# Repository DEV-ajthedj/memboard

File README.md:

# memboard
A custom development board aimed at maximizing the RAM of an RP2354A. I am doing this because I am currently developing a 3D graphics pipeline (very experimental) for microcontrollers, and an upgrade from the 264 KB Pico would be very nice for larger frambuffers and 3D objects. This is also why I didn't really need much flash on the board, so I just went with the RP2354A, which has 2MB of flash already built in. This project is meant for me to be able to really start developing and testing my pipeline more, without being limited by memory.

# Future Improvements
In the future, I hope to make firmware to make this microcontroller stackable. This could (hopefully) substantially increase the maximum compute it could generate.

# Preview

# Routing

# Schematic

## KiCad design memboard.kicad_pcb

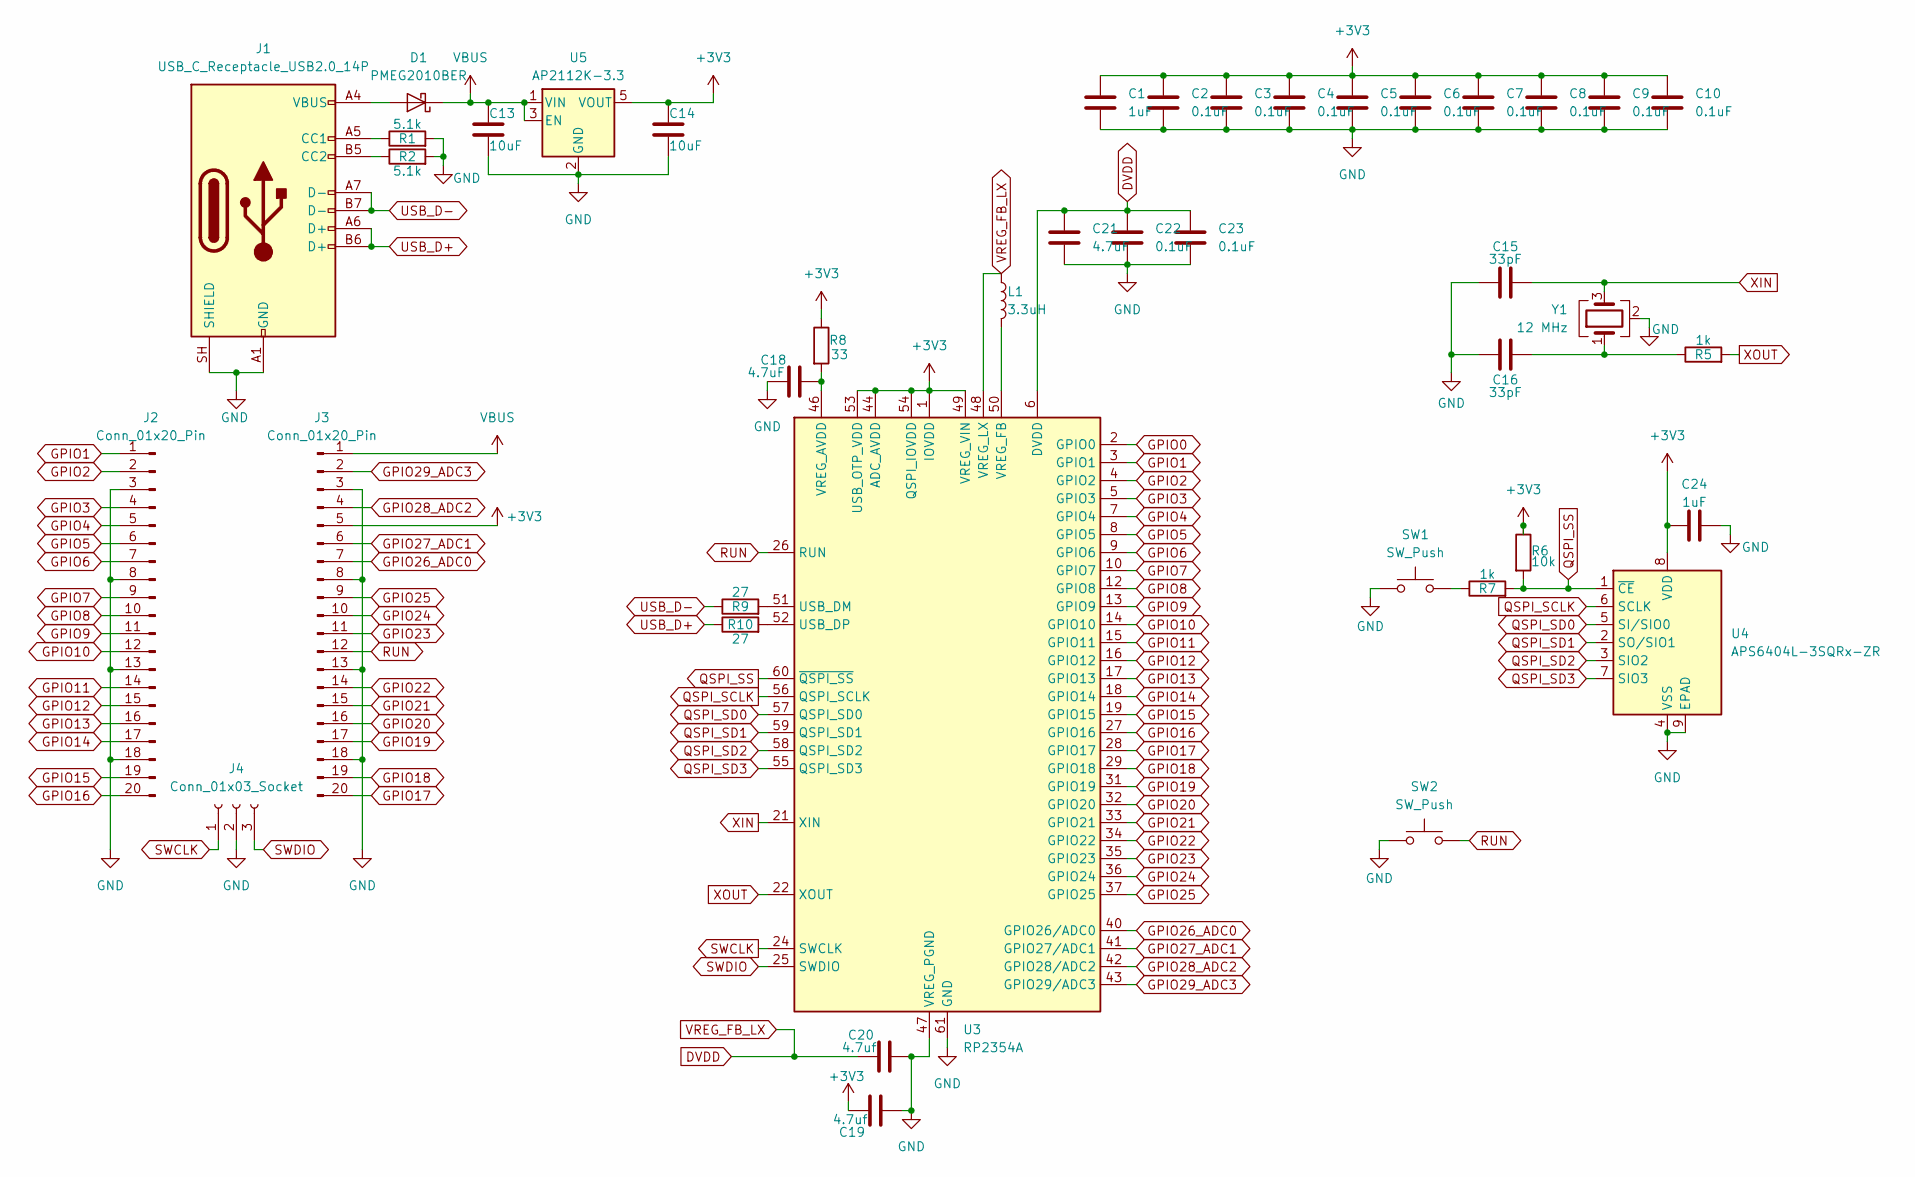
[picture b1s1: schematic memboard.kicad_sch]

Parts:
C1, C24: 1uF; C_0402_1005Metric
C2, C3, C4, C5, C6, C7, C8, C9, C10, C22, C23: 0.1uF; C_0402_1005Metric
C13, C14: 10uF; C_0603_1608Metric
C15, C16: 33pF; C_0402_1005Metric
C18, C21: 4.7uF; C_0603_1608Metric
C19, C20: 4.7uf; C_0603_1608Metric
D1: PMEG2010BER; Nexperia_CFP3_SOD-123W
J1: USB_C_Receptacle_USB2.0_14P; USB_C_Receptacle_HRO_TYPE-C-31-M-12
J2, J3: Conn_01x20_Pin; PinHeader_1x20_P2.54mm_Vertical
J4: Conn_01x03_Socket; PinSocket_1x03_P2.54mm_Vertical
L1: 3.3uH; L_0805_2012Metric
R1, R2: 5.1k; R_0402_1005Metric
R5, R7: 1k; R_0402_1005Metric
R6: 10k; R_0402_1005Metric
R8: 33; R_0402_1005Metric
R9, R10: 27; R_0402_1005Metric
SW1, SW2: SW_Push; SW_Push_SPST_NO_Alps_SKRK
U3: RP2354A; QFN-60-1EP_7x7mm_P0.4mm_EP3.4x3.4mm
U4: APS6404L-3SQRx-ZR; Winbond_USON-8-1EP_3x2mm_P0.5mm_EP0.2x1.6mm
U5: AP2112K-3.3; SOT-23-5
Y1: 12 MHz; Crystal_SMD_3225-4Pin_3.2x2.5mm

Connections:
+3V3: C1.1, C2.1, C3.1, C4.1, C5.1, C6.1, C7.1, C8.1, C9.1, C10.1, C14.1, C19.1, C24.1, J3.5, R6.1, R8.1, U3.1 (IOVDD), U3.11 (IOVDD), U3.20 (IOVDD), U3.30 (IOVDD), U3.38 (IOVDD), U3.44 (ADC_AVDD), U3.45 (IOVDD), U3.49 (VREG_VIN), U3.53 (USB_OTP_VDD), U3.54 (QSPI_IOVDD), U4.8 (VDD), U5.5 (VOUT)
DVDD: C20.1, C21.1, C22.1, C23.1, L1.1, U3.6 (DVDD), U3.23 (DVDD), U3.39 (DVDD), U3.48 (VREG_LX)
GND: C1.2, C2.2, C3.2, C4.2, C5.2, C6.2, C7.2, C8.2, C9.2, C10.2, C13.2, C14.2, C15.1, C16.1, C18.1, C19.2, C20.2, C21.2, C22.2, C23.2, C24.2, J1.A1 (GND), J1.A12 (GND), J1.B1 (GND), J1.B12 (GND), J1.SH (SHIELD), J2.3, J2.8, J2.13, J2.18, J3.3, J3.8, J3.13, J3.18, J4.2, R1.2, R2.2, SW1.1, SW2.1, U3.47 (VREG_PGND), U3.61 (GND), U4.4 (VSS), U4.9 (EPAD), U5.2 (GND), Y1.2 (G), Y1.4 (G)
GPIO0: U3.2 (GPIO0)
GPIO1: J2.1, U3.3 (GPIO1)
GPIO2: J2.2, U3.4 (GPIO2)
GPIO3: J2.4, U3.5 (GPIO3)
GPIO4: J2.5, U3.7 (GPIO4)
GPIO5: J2.6, U3.8 (GPIO5)
GPIO6: J2.7, U3.9 (GPIO6)
GPIO7: J2.9, U3.10 (GPIO7)
GPIO8: J2.10, U3.12 (GPIO8)
GPIO9: J2.11, U3.13 (GPIO9)
GPIO10: J2.12, U3.14 (GPIO10)
GPIO11: J2.14, U3.15 (GPIO11)
GPIO12: J2.15, U3.16 (GPIO12)
GPIO13: J2.16, U3.17 (GPIO13)
GPIO14: J2.17, U3.18 (GPIO14)
GPIO15: J2.19, U3.19 (GPIO15)
GPIO16: J2.20, U3.27 (GPIO16)
GPIO17: J3.20, U3.28 (GPIO17)
GPIO18: J3.19, U3.29 (GPIO18)
GPIO19: J3.17, U3.31 (GPIO19)
GPIO20: J3.16, U3.32 (GPIO20)
GPIO21: J3.15, U3.33 (GPIO21)
GPIO22: J3.14, U3.34 (GPIO22)
GPIO23: J3.11, U3.35 (GPIO23)
GPIO24: J3.10, U3.36 (GPIO24)
GPIO25: J3.9, U3.37 (GPIO25)
GPIO26_ADC0: J3.7, U3.40 (GPIO26/ADC0)
GPIO27_ADC1: J3.6, U3.41 (GPIO27/ADC1)
GPIO28_ADC2: J3.4, U3.42 (GPIO28/ADC2)
GPIO29_ADC3: J3.2, U3.43 (GPIO29/ADC3)
unnamed: C16.2, R5.1, Y1.1
unnamed: D1.2 (A), J1.A4 (VBUS), J1.A9 (VBUS), J1.B4 (VBUS), J1.B9 (VBUS)
unnamed: J1.A5 (CC1), R1.1
unnamed: J1.B5 (CC2), R2.1
unnamed: R7.1, SW1.2
unnamed: R9.2, U3.51 (USB_DM)
unnamed: R10.2, U3.52 (USB_DP)
unnamed: C18.2, R8.2, U3.46 (VREG_AVDD)
unnamed: L1.2, U3.50 (VREG_FB)
QSPI_SCLK: U3.56 (QSPI_SCLK), U4.6 (SCLK)
QSPI_SD0: U3.57 (QSPI_SD0), U4.5 (SI/SIO0)
QSPI_SD1: U3.59 (QSPI_SD1), U4.2 (SO/SIO1)
QSPI_SD2: U3.58 (QSPI_SD2), U4.3 (SIO2)
QSPI_SD3: U3.55 (QSPI_SD3), U4.7 (SIO3)
QSPI_SS: R6.2, R7.2, U3.60 (~QSPI_SS), U4.1 (~CE)
RUN: J3.12, SW2.2, U3.26 (RUN)
SWCLK: J4.1, U3.24 (SWCLK)
SWDIO: J4.3, U3.25 (SWDIO)
USB_D+: J1.A6 (D+), J1.B6 (D+), R10.1
USB_D-: J1.A7 (D-), J1.B7 (D-), R9.1
VBUS: C13.1, D1.1 (K), J3.1, U5.1 (VIN), U5.3 (EN)
XIN: C15.2, U3.21 (XIN), Y1.3
XOUT: R5.2, U3.22 (XOUT)

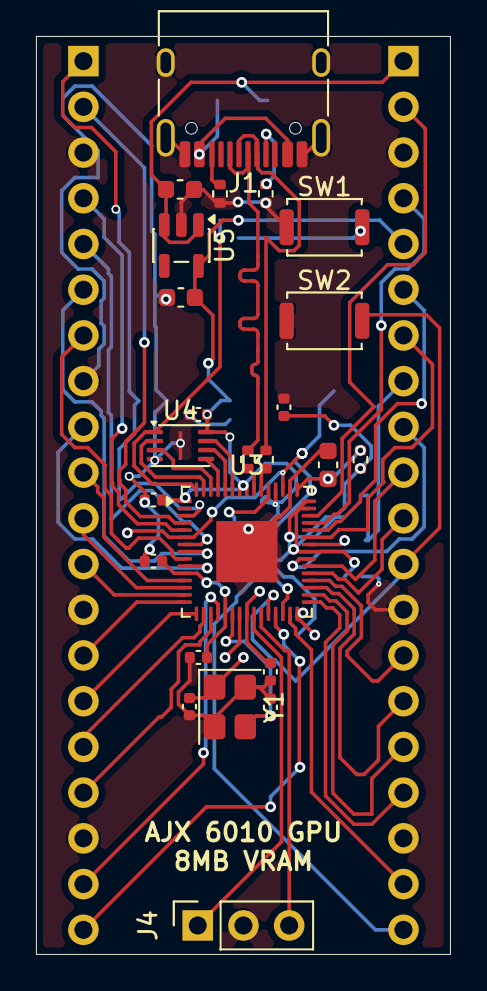
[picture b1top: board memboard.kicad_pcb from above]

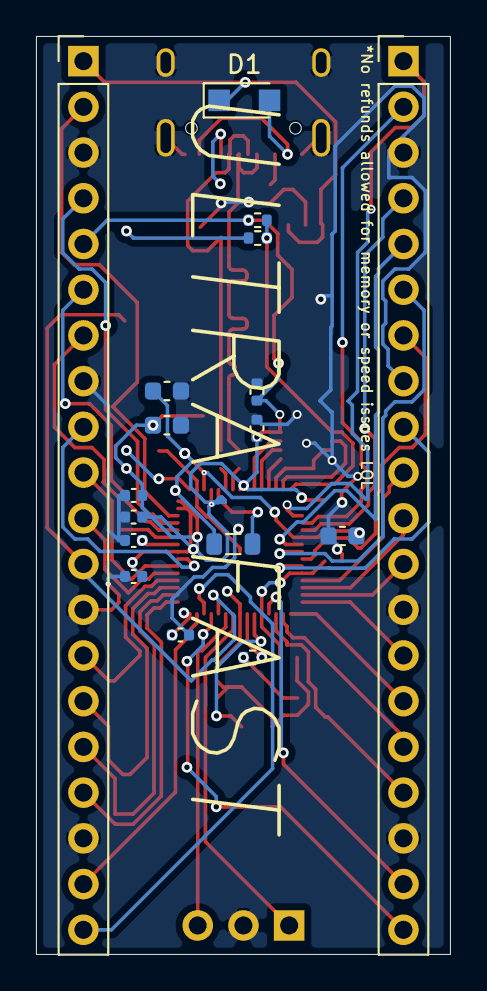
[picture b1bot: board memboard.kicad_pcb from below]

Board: 4 copper layers, 23.0 x 51.0 mm, 41 parts (17 on the bottom side), 55 nets.

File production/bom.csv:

Designator,Footprint,Quantity,Value,LCSC Part #
"C1, C24",0402,2,1uF,
"C10, C2, C22, C23, C3, C4, C5, C6, C7, C8, C9",0402,11,0.1uF,
"C13, C14",0603,2,10uF,
"C15, C16",0402,2,33pF,
"C18, C19, C20, C21",0603,4,4.7uF,
J1,USB_C_Receptacle_HRO_TYPE-C-31-M-12,1,USB_C_Receptacle_USB2.0_14P,
"J2, J3",PinHeader_1x20_P2.54mm_Vertical,2,Conn_01x20_Pin,
J4,PinSocket_1x03_P2.54mm_Vertical,1,Conn_01x03_Socket,
L1,0805,1,3.3uH,
"R1, R2",0402,2,5.1k,
"R10, R9",0402,2,27,
"R5, R7",0402,2,1k,
R6,0402,1,10k,
R8,0402,1,33,
"SW1, SW2",SW_Push_SPST_NO_Alps_SKRK,2,SW_Push,
U3,QFN-60-1EP_7x7mm_P0.4mm_EP3.4x3.4mm,1,RP2354A,
U4,Winbond_USON-8-1EP_3x2mm_P0.5mm_EP0.2x1.6mm,1,APS6404L-3SQRx-ZR,
U5,SOT-23-5,1,AP2112K-3.3,
Y1,Crystal_SMD_3225-4Pin_3.2x2.5mm,1,12 MHz,

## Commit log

2026-04-21 Finished Design
2026-04-21 Changed README
2026-04-21 Include image in README for memboard project
    Add image to README for visual reference
2026-04-21 Add preview image to README
    Added a preview image section to the README.
2026-04-24 Enhance README with project details and future plans
    Expanded project description and added future improvement plans.
2026-04-24 Add schematic image to README
2026-05-03 Added a Schottky diode to allow power through VBUS because USB-C cannot be back powered
